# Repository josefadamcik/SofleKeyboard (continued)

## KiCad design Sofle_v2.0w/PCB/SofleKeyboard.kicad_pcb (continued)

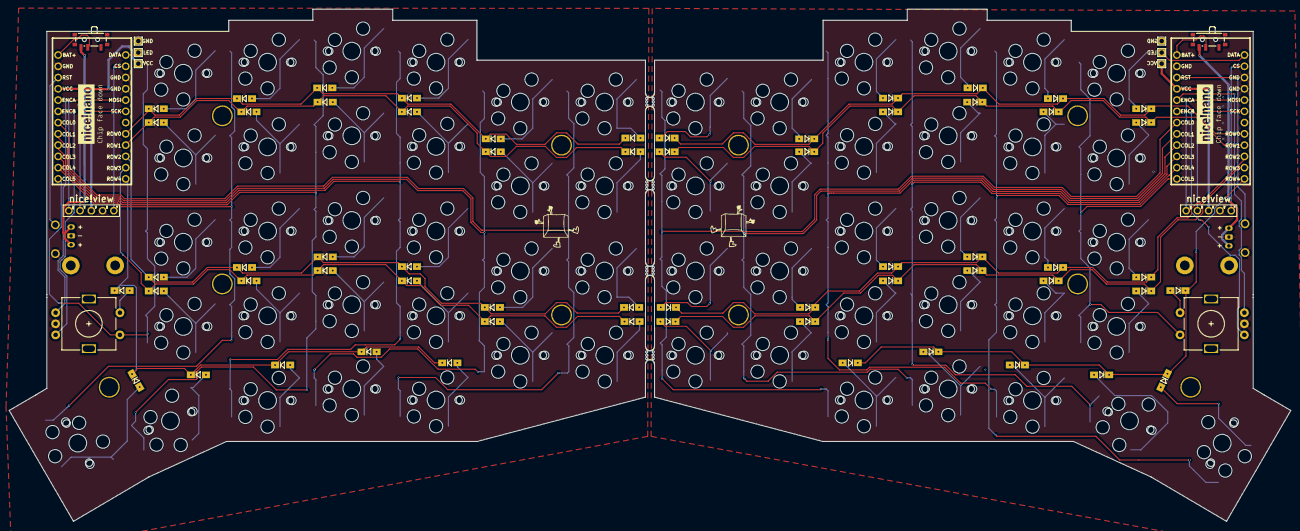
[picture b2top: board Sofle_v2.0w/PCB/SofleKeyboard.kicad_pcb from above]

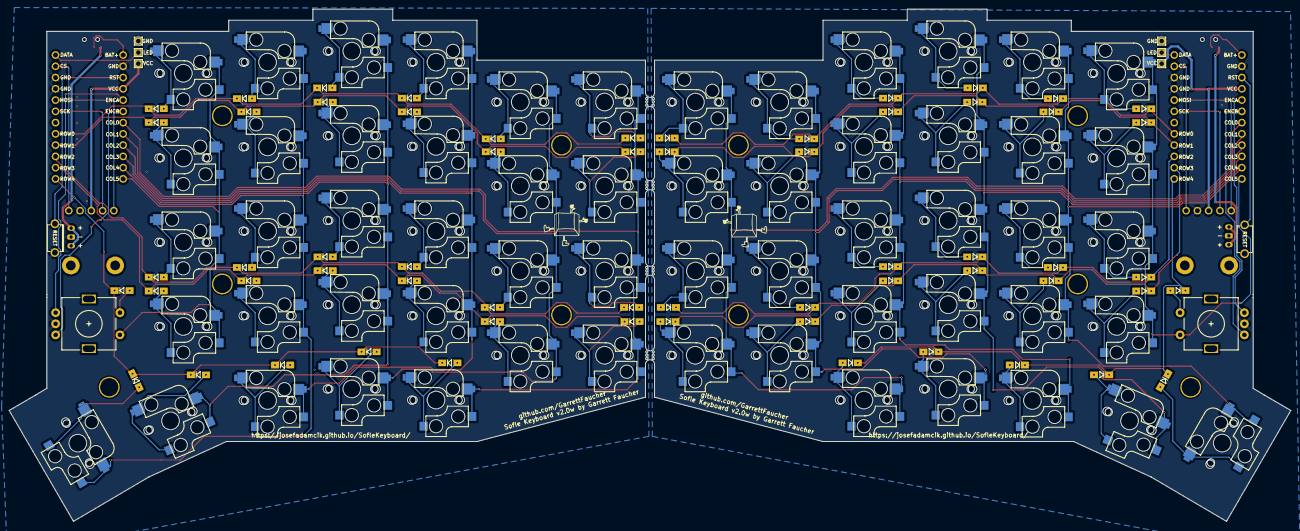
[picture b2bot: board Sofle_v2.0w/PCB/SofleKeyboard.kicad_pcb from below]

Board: 2 copper layers, 289.0 x 115.5 mm, 150 parts (2 on the bottom side), 102 nets.

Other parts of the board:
mouse-bite-2mm-slot, mouse-bite-2mm-slot#2, mouse-bite-2mm-slot#3, mouse-bite-2mm-slot#4: VAL**; mouse-bite-2mm-slot

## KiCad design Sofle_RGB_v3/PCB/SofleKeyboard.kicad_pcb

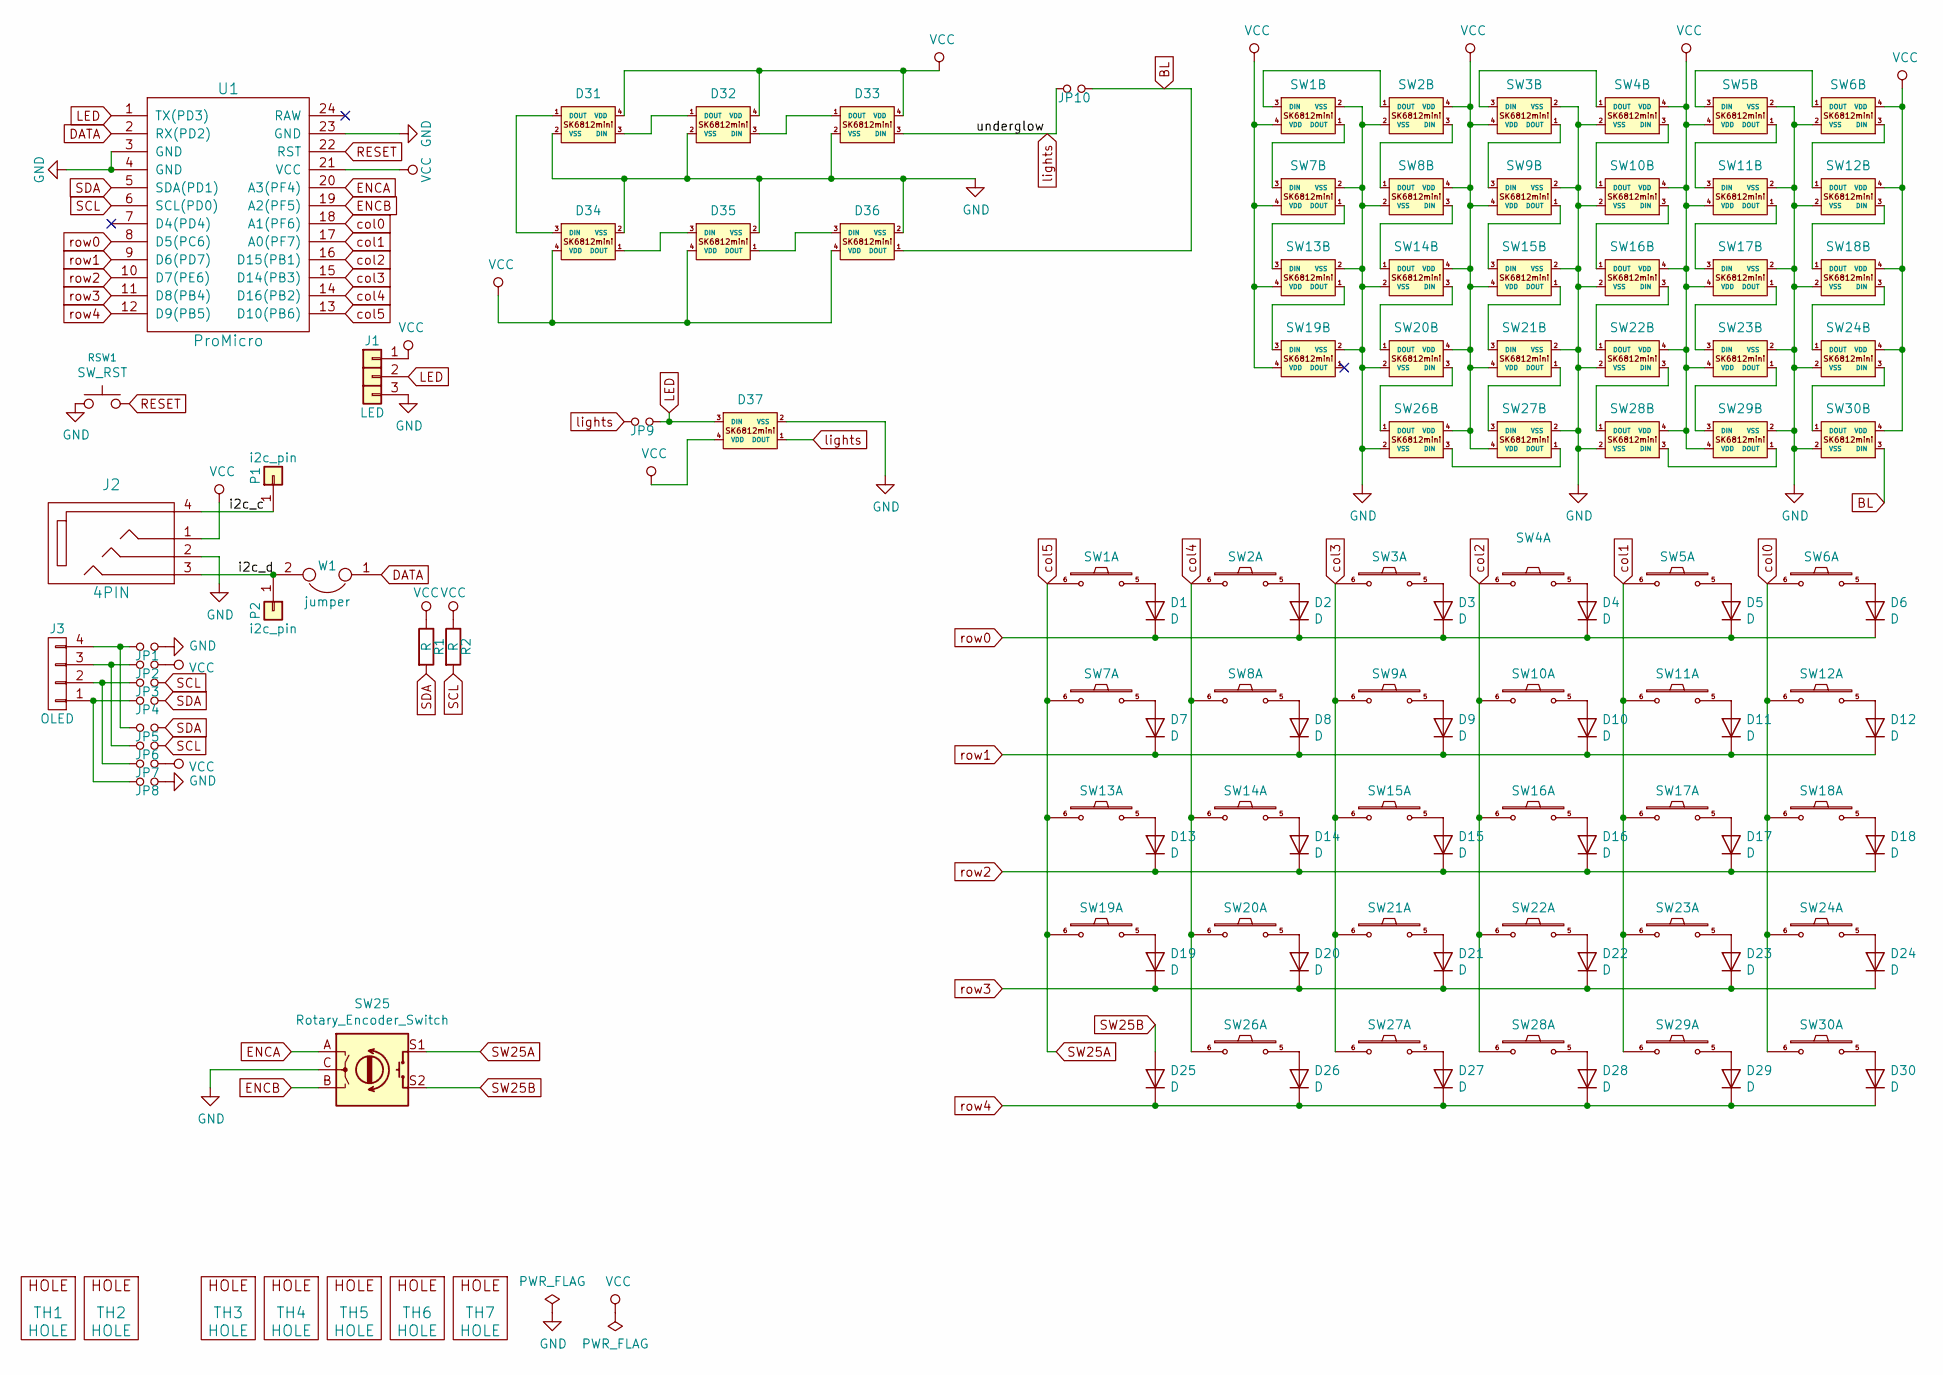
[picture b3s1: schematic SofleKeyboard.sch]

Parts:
D1, D2, D3, D4, D5, D6, D7, D8, D9, D10, D11, D12, D13, D14, D15, D16, D17, D18, D19, D20, D21, D22, D23, D24, D25, D26, D27, D28, D29, D30: D; crkbd-diode
D31, D32, D33, D34, D35, D36, D37: LED_sk2812_SM; SK6812MINI_underglow_dev_Silk_GND
J1: LED
J2: 4PIN; MJ-4PP-9
J3: OLED; OLED_4Pin
JP1, JP2, JP3, JP4, JP5, JP6, JP7, JP8, JP9, JP10: Jumper_NO_Small; Jumper
P1, P2: i2c_pin; 1pin_conn
R1, R2: R; RESISTOR_mini
RSW1: SW_RST; TACT_SWITCH_TVBP06
SW1, SW2, SW3, SW4, SW5, SW6, SW7, SW8, SW9, SW10, SW11, SW12, SW13, SW14, SW15, SW16, SW17, SW18, SW19, SW20, SW21, SW22, SW23, SW24, SW26, SW27, SW28, SW29, SW30: SW_PUSH-MX_W_LED; SK6812MINI_and_cherry_Silk_GND
SW25: Rotary_Encoder_Switch; RotaryEncoder_Alps_EC11E-Switch_Vertical_H20mm-keebio_modif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
TH1, TH2: HOLE; M2_HOLE_PCB
TH3, TH4, TH5, TH6, TH7: HOLE; HOLE_M2_TH
U1: ProMicro
W1: jumper; jumper_data

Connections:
/i2c_c: J2.4, P1.1
/i2c_d: J2.3, P2.1, W1.2
BL: D36.1 (DOUT), JP10.2, SW30.3 (DIN)
DATA: U1.2 (RX(PD2)), W1.1
ENCA: SW25.A, U1.20 (A3(PF4))
ENCB: SW25.B, U1.19 (A2(PF5))
GND: D31.2 (VSS), D32.2 (VSS), D33.2 (VSS), D34.2 (VSS), D35.2 (VSS), D36.2 (VSS), D37.2 (VSS), J1.3, J2.2, JP1.2, JP8.2, RSW1.1, SW1.2 (VSS), SW2.2 (VSS), SW3.2 (VSS), SW4.2 (VSS), SW5.2 (VSS), SW6.2 (VSS), SW7.2 (VSS), SW8.2 (VSS), SW9.2 (VSS), SW10.2 (VSS), SW11.2 (VSS), SW12.2 (VSS), SW13.2 (VSS), SW14.2 (VSS), SW15.2 (VSS), SW16.2 (VSS), SW17.2 (VSS), SW18.2 (VSS), SW19.2 (VSS), SW20.2 (VSS), SW21.2 (VSS), SW22.2 (VSS), SW23.2 (VSS), SW24.2 (VSS), SW25.C, SW26.2 (VSS), SW27.2 (VSS), SW28.2 (VSS), SW29.2 (VSS), SW30.2 (VSS), U1.3 (GND), U1.4 (GND), U1.23 (GND)
LED: D37.3 (DIN), J1.2, JP9.2, U1.1 (TX(PD3))
unnamed: D1.2 (A), SW1.5
unnamed: D2.2 (A), SW2.5
unnamed: D3.2 (A), SW3.5
unnamed: D4.2 (A), SW4.5
unnamed: D5.2 (A), SW5.5
unnamed: D6.2 (A), SW6.5
unnamed: D7.2 (A), SW7.5
unnamed: D8.2 (A), SW8.5
unnamed: D9.2 (A), SW9.5
unnamed: D10.2 (A), SW10.5
unnamed: D11.2 (A), SW11.5
unnamed: D12.2 (A), SW12.5
unnamed: D13.2 (A), SW13.5
unnamed: D14.2 (A), SW14.5
unnamed: D15.2 (A), SW15.5
unnamed: D16.2 (A), SW16.5
unnamed: D17.2 (A), SW17.5
unnamed: D18.2 (A), SW18.5
unnamed: D19.2 (A), SW19.5
unnamed: D20.2 (A), SW20.5
unnamed: D21.2 (A), SW21.5
unnamed: D22.2 (A), SW22.5
unnamed: D23.2 (A), SW23.5
unnamed: D24.2 (A), SW24.5
unnamed: D26.2 (A), SW26.5
unnamed: D27.2 (A), SW27.5
unnamed: D28.2 (A), SW28.5
unnamed: D29.2 (A), SW29.5
unnamed: D30.2 (A), SW30.5
unnamed: D31.1 (DOUT), D34.3 (DIN)
unnamed: D31.3 (DIN), D32.1 (DOUT)
unnamed: D32.3 (DIN), D33.1 (DOUT)
unnamed: D34.1 (DOUT), D35.3 (DIN)
unnamed: D35.1 (DOUT), D36.3 (DIN)
unnamed: J3.1, JP4.1, JP8.1
unnamed: J3.2, JP3.1, JP7.1
unnamed: J3.3, JP2.1, JP6.1
unnamed: J3.4, JP1.1, JP5.1
unnamed: SW1.1 (DOUT), SW7.3 (DIN)
unnamed: SW1.3 (DIN), SW2.1 (DOUT)
unnamed: SW2.3 (DIN), SW8.1 (DOUT)
unnamed: SW3.1 (DOUT), SW9.3 (DIN)
unnamed: SW3.3 (DIN), SW4.1 (DOUT)
unnamed: SW5.3 (DIN), SW6.1 (DOUT)
unnamed: SW4.3 (DIN), SW10.1 (DOUT)
unnamed: SW10.3 (DIN), SW16.1 (DOUT)
unnamed: SW11.1 (DOUT), SW17.3 (DIN)
unnamed: SW5.1 (DOUT), SW11.3 (DIN)
unnamed: SW6.3 (DIN), SW12.1 (DOUT)
unnamed: SW12.3 (DIN), SW18.1 (DOUT)
unnamed: SW13.1 (DOUT), SW19.3 (DIN)
unnamed: SW7.1 (DOUT), SW13.3 (DIN)
unnamed: SW8.3 (DIN), SW14.1 (DOUT)
unnamed: SW14.3 (DIN), SW20.1 (DOUT)
unnamed: SW15.1 (DOUT), SW21.3 (DIN)
unnamed: SW9.1 (DOUT), SW15.3 (DIN)
unnamed: SW16.3 (DIN), SW22.1 (DOUT)
unnamed: SW17.1 (DOUT), SW23.3 (DIN)
unnamed: SW18.3 (DIN), SW24.1 (DOUT)
unnamed: SW20.3 (DIN), SW26.1 (DOUT)
unnamed: SW21.1 (DOUT), SW27.3 (DIN)
unnamed: SW22.3 (DIN), SW28.1 (DOUT)
unnamed: SW23.1 (DOUT), SW29.3 (DIN)
unnamed: SW24.3 (DIN), SW30.1 (DOUT)
unnamed: SW26.3 (DIN), SW27.1 (DOUT)
unnamed: SW28.3 (DIN), SW29.1 (DOUT)
RESET: RSW1.2, U1.22 (RST)
SCL: JP3.2, JP6.2, R2.2, U1.6 (SCL(PD0))
SDA: JP4.2, JP5.2, R1.2, U1.5 (SDA(PD1))
SW25A: SW1.6, SW7.6, SW13.6, SW19.6, SW25.S1, U1.13 (D10(PB6))
SW25B: D25.2 (A), SW25.S2
VCC: D31.4 (VDD), D32.4 (VDD), D33.4 (VDD), D34.4 (VDD), D35.4 (VDD), D36.4 (VDD), D37.4 (VDD), J1.1, J2.1, JP2.2, JP7.2, R1.1, R2.1, SW1.4 (VDD), SW2.4 (VDD), SW3.4 (VDD), SW4.4 (VDD), SW5.4 (VDD), SW6.4 (VDD), SW7.4 (VDD), SW8.4 (VDD), SW9.4 (VDD), SW10.4 (VDD), SW11.4 (VDD), SW12.4 (VDD), SW13.4 (VDD), SW14.4 (VDD), SW15.4 (VDD), SW16.4 (VDD), SW17.4 (VDD), SW18.4 (VDD), SW19.4 (VDD), SW20.4 (VDD), SW21.4 (VDD), SW22.4 (VDD), SW23.4 (VDD), SW24.4 (VDD), SW26.4 (VDD), SW27.4 (VDD), SW28.4 (VDD), SW29.4 (VDD), SW30.4 (VDD), U1.21 (VCC)
col0: SW6.6, SW12.6, SW18.6, SW24.6, SW30.6, U1.18 (A1(PF6))
col1: SW5.6, SW11.6, SW17.6, SW23.6, SW29.6, U1.17 (A0(PF7))
col2: SW4.6, SW10.6, SW16.6, SW22.6, SW28.6, U1.16 (D15(PB1))
col3: SW3.6, SW9.6, SW15.6, SW21.6, SW27.6, U1.15 (D14(PB3))
col4: SW2.6, SW8.6, SW14.6, SW20.6, SW26.6, U1.14 (D16(PB2))
lights: D33.3 (DIN), D37.1 (DOUT), JP9.1, JP10.1
row0: D1.1 (K), D2.1 (K), D3.1 (K), D4.1 (K), D5.1 (K), D6.1 (K), U1.8 (D5(PC6))
row1: D7.1 (K), D8.1 (K), D9.1 (K), D10.1 (K), D11.1 (K), D12.1 (K), U1.9 (D6(PD7))
row2: D13.1 (K), D14.1 (K), D15.1 (K), D16.1 (K), D17.1 (K), D18.1 (K), U1.10 (D7(PE6))
row3: D19.1 (K), D20.1 (K), D21.1 (K), D22.1 (K), D23.1 (K), D24.1 (K), U1.11 (D8(PB4))
row4: D25.1 (K), D26.1 (K), D27.1 (K), D28.1 (K), D29.1 (K), D30.1 (K), U1.12 (D9(PB5))

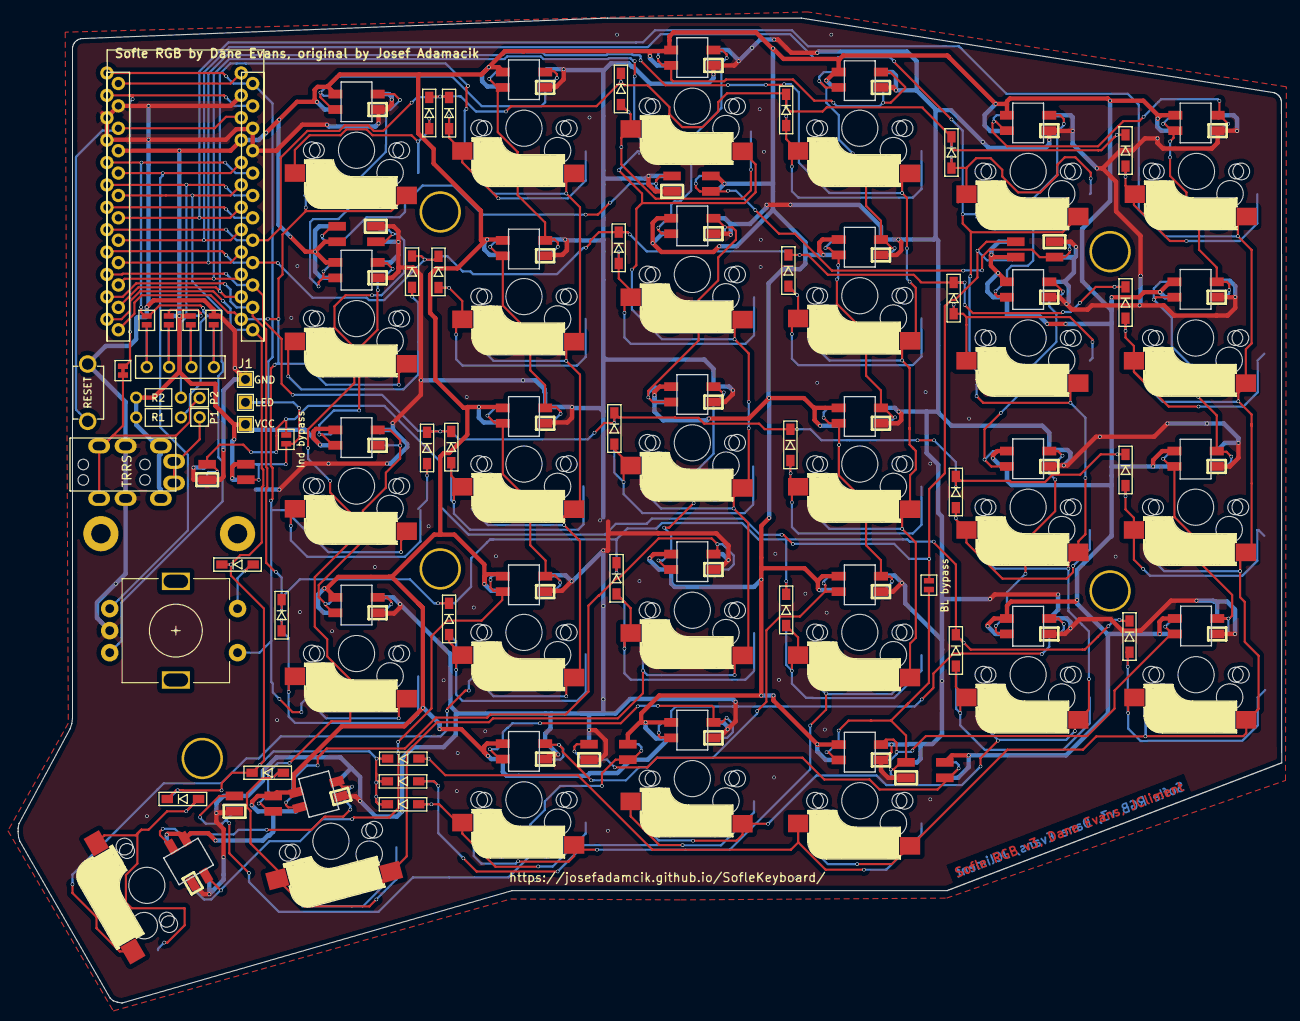
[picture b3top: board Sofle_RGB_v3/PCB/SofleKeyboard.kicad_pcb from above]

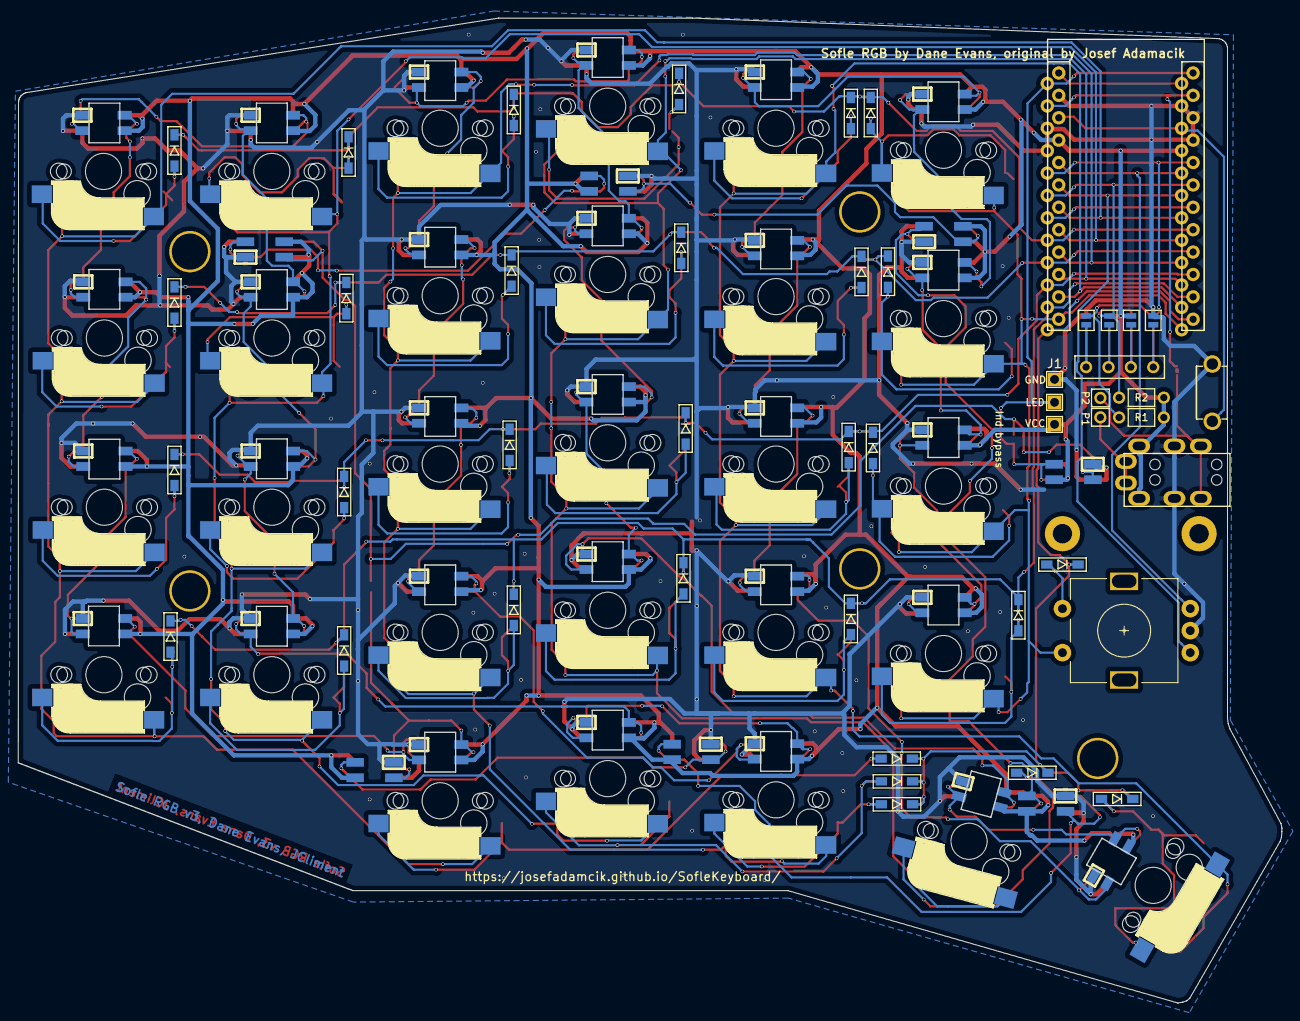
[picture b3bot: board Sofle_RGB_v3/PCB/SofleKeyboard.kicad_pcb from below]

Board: 2 copper layers, 143.4 x 111.8 mm, 94 parts (4 on the bottom side), 91 nets.

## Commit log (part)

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2019-09-28 Add PCB files
2019-09-28 Add footprints
2019-09-28 Add design files (SVG)
2019-09-28 Add readme and gitignore.
2019-09-29 Fix left edge
2019-09-29 SVG: new layer for the top plate, copy cutouts for switches there
2019-09-29 First top case version in kicad
2019-09-29 Bottom case in kicad
2019-09-29 Clean some unused footprints
2019-09-30 Add first version of logo
2019-10-14 Finish logo, add the logo and credits on the bottom plate
2019-10-14 Update footprints, gitignore and shape
2019-10-14 Small details.
2019-10-14 Add renders of PCB
2019-11-10 Update readme - add images and a link to the firwmare
2020-01-26 Add new image
2020-02-26 Add links to the blog-post and to the build guide/log article
2020-03-01 Add archives with gerber files
2020-03-14 Move footprint library
2020-03-14 Adde submodule with Keebio-Parts.pretty
2020-03-15 Add a photo withc chocs
2020-03-15 Readme: link to releases instead of directory with gerbers in the source tree
2020-03-16 Moving bottom row
2020-04-10 Stagger changed, cleaning and fixing routing for keys
2020-04-10 WIP routing micro
2020-04-11 WIP routing matrix
2020-04-14 Add very rough Edge
2020-04-16 Adding 3d models
2020-04-16 First renders of version 2
2020-04-17 Experimenting with outline
2020-04-28 Image of adjust layer
2020-04-30 updated image of adjust layer
2020-04-30 New edge
2020-05-01 New shapes for top and bottom plates
2020-05-04 Add logos and credits on all boards
2020-05-04 Set theme jekyll-theme-cayman
2020-05-05 Finalized, gerbers exported
2020-05-11 Fix missing soldermask on pcb
2020-05-18 licence for documentation
2020-06-11 WIP build guide and sourcing guide in the docuentation.
2020-06-11 Images for build guide, improvements for the build guide
2020-06-11 add matomo, try to fix docs site
2020-06-11 Minor fixes in readme
2020-08-13 URL of the build guide fixed
2020-12-21 de.aliexpress -> www.ali
2020-12-24 added Sofle RGB to upstream v2 including gerber release pcb files based on sofle v2 with up to 36 leds added plates for rgb version with tenting using m3/m4 bolts and thumb screws oled cover plate - 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
2021-01-16 Start changing the structure. Most of the files are only copied around Inso Sofle_v1 subdirectory. The structure update is going to be finished once this is merged with the develop branch
2021-01-16 Update documentation - info about versions. Move build guide for RGB to documentation. Link things properly.
2021-01-16 Fix missing sym-lib-table for RGB (missing symbols in shchematic)
2021-01-16 Add OLED cover for version 1
2021-01-16 Generate gerber files for v2, remove raw gerbers from repository
2021-01-16 Fix link to oled cover for RGB
2021-01-16 Add info about OLED covers for version 1
2021-02-01 Update sourcing_parts.md
    Remove the link to mysticmechs, there group buy ended up quite some time ago and they appear to have some issues. Also, there have been plenty of vendors selling sofle since then, no reason to promot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
2021-02-04 Fix #34 - a mistake in the edge-cut layer of version 2, gerbers updated too
2021-02-27 fixed bug in v2.0, upversioned
2021-03-05 remove Sofle_RGB/Build_guide dir
2021-03-09 updated footprints to mini-e, have broken the pinout from the datasheet in order to avoid doing a schematic revision. and removed local traces
2021-03-17 Return back the image for rgb via issue, fix the link from build guide
2021-03-28 another split kb project
2021-04-07 Update build_guide_rgb.md
    Fix LED table issues, a few changes to layout, spelling mistakes and formatting while I was in here anyway
2021-04-07 Update issue templates
    See #58
2021-04-07 testing
2021-04-07 fix up default titles
2021-04-08 Fix table being one line
2021-04-08 Fix wrong pins to short
2021-04-09 Delete issue.md
    Remove the default one so that the others show up
2021-04-09 fixed up lighting configuration
2021-05-07 Update build_guide_rgb.md
    fix up the rgb table, and made it more obvious,
    Also sorted it in a more usable way, no idea what I was thinking before
2021-05-26 fix up issue template tags
2021-05-30 Updated flashing instructions, put emphasis on QMK documentation
2021-06-17 Address PR comments + extra cleanup
2021-06-19 Fix wrong link to qmk documentation
2021-06-19 Fix typo "follow"
2021-07-11 plates in svg format for v2
2021-07-17 tenting case for rgb
2021-08-14 Fix traces too close to pads
2021-08-14 Better LED orientation marks
2021-08-14 Enlarge encoder cutout by 1mm
2021-08-14 Bump to version 2.1
2021-08-14 Sofle Choc Build Guide
2021-08-22 Update index.md
    Fix typos
2021-08-22 Update build_guide.md
    Mention there's a dedicated build guide for the RGB version since apparently some people haven't noticed yet.
2021-08-22 Update build_guide_rgb.md
    add keyhive warning
2021-08-22 Update build_guide_rgb.md
    a
2021-08-22 Update index.md
    a
2021-08-22 Update build_guide_rgb.md
    Link to the build guide
2021-09-28 Bump nokogiri from 1.11.5 to 1.12.5 in /docs
    Bumps [nokogiri](https://github.com/sparklemotion/nokogiri) from 1.11.5 to 1.12.5.
    - [Release notes](https://github.com/sparklemotion/nokogiri/releases)
    - [Changelog](https://github.com/sparklemotion/nokogiri/blob/main/CHANGELOG.md)
    - [Commits](https://github.com/sparklemotion/nokogiri/compare/v1.11.5...v1.12.5)
    ---
    updated-dependencies:
2021-10-10 Rename folder Choc_v2 -> Choc
2021-10-10 Remove version number from source files (use git instead)
2021-10-15 add 3D printable case
2021-10-15 remove link from Sofle_v1/Case/3D_Print/README.md
2021-11-12 Improve build guide
2021-11-14 add missing 3D case .stl files
2021-11-14 Add Choc to the issue templates
2021-11-14 adding lower plate files back in. I have no idea where or how they dissappeared
2021-11-19 fix filename
2021-11-19 update README for 3d case
2021-12-19 Update build_guide_rgb.md: flash rgb firmware
    flash rgb_default instead of default, otherwise the lights don't light up (needed for testing LEDs during the build process)
2021-12-23 Thicken top plate above encoder
2021-12-23 Fix labels for the RGB connector.
2021-12-23 Updated gerber files.
2021-12-27 More fixes on GND/VCC tracks.
2022-01-06 Update build_guide_rgb.md
    Fixed two typos:
    - Importand -> Important
    - desing -> design
2022-01-30 Sofle Choc: kits
2022-01-30 Sofle Choc: socketing ProMicro and OLED
2022-01-30 Correct VIA firmware instructions
2022-02-26 Bump nokogiri from 1.12.5 to 1.13.3 in /docs
    Bumps [nokogiri](https://github.com/sparklemotion/nokogiri) from 1.12.5 to 1.13.3.
    - [Release notes](https://github.com/sparklemotion/nokogiri/releases)
    - [Changelog](https://github.com/sparklemotion/nokogiri/blob/main/CHANGELOG.md)
    - [Commits](https://github.com/sparklemotion/nokogiri/compare/v1.12.5...v1.13.3)
    ---
    updated-dependencies:
2022-04-20 Oled covers for Sofle V2
2022-05-05 Updated build guide + kits link
2022-05-19 Bump nokogiri from 1.12.5 to 1.13.6 in /docs
    Bumps [nokogiri](https://github.com/sparklemotion/nokogiri) from 1.12.5 to 1.13.6.
    - [Release notes](https://github.com/sparklemotion/nokogiri/releases)
    - [Changelog](https://github.com/sparklemotion/nokogiri/blob/main/CHANGELOG.md)
    - [Commits](https://github.com/sparklemotion/nokogiri/compare/v1.12.5...v1.13.6)
    ---
    updated-dependencies:
2022-07-05 Fix broken "build guide choc" link
2022-07-05 Fix table in soflergb build guide
2022-07-28 add soldered PCB version
2022-08-18 rename folders for layout indication
2022-08-18 remove autogenerated kicad backup files
2023-01-18 Bump nokogiri from 1.13.9 to 1.14.0 in /docs
    Bumps [nokogiri](https://github.com/sparklemotion/nokogiri) from 1.13.9 to 1.14.0.
    - [Release notes](https://github.com/sparklemotion/nokogiri/releases)
    - [Changelog](https://github.com/sparklemotion/nokogiri/blob/main/CHANGELOG.md)
    - [Commits](https://github.com/sparklemotion/nokogiri/compare/v1.13.9...v1.14.0)
    ---
    updated-dependencies:
2023-03-21 Updated qmk getting started link in build guide for sofle choc
2023-04-09 add kofi
2023-04-09 add kofi to readme
2023-04-13 Add tended case file for V2
2023-05-25 Initial files
2023-05-25 Don't need git backups
2023-05-26 Added all components
2023-05-26 Minor tweaks
2023-05-26 Routed right half
2023-05-26 I fit both pcbs in and routed a little
2023-05-26 Added mouse bites and fixed some diodes
2023-05-26 Removed gerbers
2023-05-26 Cleaning
2023-05-26 Added visual changes
2023-05-27 First try complete
2023-05-27 Better silk screen
2023-05-28 Updated silk screen and fixed bad traces
2023-07-14 Refocus layer
2023-07-17 Upload gerber
2023-07-17 Deleted changes made to original Sofle v2
2024-02-17 Sofle Pico index content added
2024-02-21 Added sofle pico core files Added sofle pico to jekyll navigation template
2024-03-04 Adds favicons html as an include Adds favicon images and manifests in seperate directory
2024-03-24 Excludes Sofle Pico backups from repo
2024-03-24 Adds Sofle Pico credit to main README
2024-03-24 updated contributor name for consistency
2024-03-24 Bumps gem github-pages and adds webrick
2024-05-05 Fixed some bad routing, needs to be vetted
2024-11-18 Removed metadata from images
2025-06-20 Fix PCB file regression to v1. Gerbers were corret at v1.1
2025-06-20 Bump nokogiri from 1.14.3 to 1.18.8 in /docs
    Bumps [nokogiri](https://github.com/sparklemotion/nokogiri) from 1.14.3 to 1.18.8.
    - [Release notes](https://github.com/sparklemotion/nokogiri/releases)
    - [Changelog](https://github.com/sparklemotion/nokogiri/blob/main/CHANGELOG.md)
    - [Commits](https://github.com/sparklemotion/nokogiri/compare/v1.14.3...v1.18.8)
    ---
    updated-dependencies:
2025-06-21 Bump uri from 0.13.0 to 0.13.2 in /docs
    Bumps [uri](https://github.com/ruby/uri) from 0.13.0 to 0.13.2.
    - [Release notes](https://github.com/ruby/uri/releases)
    - [Commits](https://github.com/ruby/uri/compare/v0.13.0...v0.13.2)
    ---
    updated-dependencies:
    - dependency-name: uri
2025-06-21 Bump rexml from 3.2.6 to 3.3.9 in /docs
    Bumps [rexml](https://github.com/ruby/rexml) from 3.2.6 to 3.3.9.
    - [Release notes](https://github.com/ruby/rexml/releases)
    - [Changelog](https://github.com/ruby/rexml/blob/master/NEWS.md)
    - [Commits](https://github.com/ruby/rexml/compare/v3.2.6...v3.3.9)
    ---
    updated-dependencies:
2025-12-30 Bump uri from 0.13.2 to 0.13.3 in /docs
    Bumps [uri](https://github.com/ruby/uri) from 0.13.2 to 0.13.3.
    - [Release notes](https://github.com/ruby/uri/releases)
    - [Commits](https://github.com/ruby/uri/compare/v0.13.2...v0.13.3)
    ---
    updated-dependencies:
    - dependency-name: uri
